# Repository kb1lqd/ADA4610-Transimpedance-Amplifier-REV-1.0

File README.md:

Notes

# 2022-08-23

* Soldered the board together
* It works! But I did find some minor errors.
* The voltage output varies as expected with light over a wide range

## Errors
* D1 footprint pin 1 assingment is backwards, this resulted in the diode being backwards
* The resulting current from the device is quite large resulting in the second amplifier stage being saturate in a lit room, I removed R7 to create a voltage follower and this alleviate the issues for now
* Placing the output on a scope it's clear there is a HF oscillation at 2.24mHz
** NOTE that the oscillation appears to be only on the 2nd stage output and not the first stage. Note that the second stage is now a voltage follower

# 2022-08-24

* Placed a 33pF capacitor across R8 and this stopped the oscillation
* I repopulated R7 with a 1K resistor
* There is some very very high frequency noise but pretty negligable it seems
* It works! I can definetley see an IRDA remote control signal at ~37KHz carrier
* It seems like if I want to use this in a bright room I'm going to have to turn the gains down
** Which is better - the TIA or the second stage?

# 2022-10-03

I've built up a bit of infrastructure around this TIA:
* Headphone amplifier to output the audio frequencies directly into headphones
* Listened to external light sources with a len assembly 3 miles away
* Built a simple audio light transmitter

I've noticed a faire bit of noise in the circuit. Hooking a scope up to the TP output I see a fairly complex oscillation between 30KHz and 97KHz. There is a different noise on the TIA output directly much smaller prior to the line driver amplifier.

**Noise on the TIA PCB 50 Ohm Output***

**Noise on the TIA Output directly**

I can see and hear the 120 Hz hum from my indoor (dim) lights that this noise is on top of.

# 2022-10-04

* I put the recommended bulk capacitors on the PYBE20-Q24-D5-T - No significant change but leaving them There
* I think it may have knocked a bit of the switching noise off
  * I defintely see a 32KHz DC/DC switching noise but it's near my scopes limit
  * It is seen on the preamp section op-amp bulk capacitors and in the TIA signal itself - It may be ground noise coming through the GND clip...?
  * Placing bulk capacitance on the preamp - no effect
* I added a 15pF capacitor to C2 to help bypass any HF signals past the 0 ohm or stabalize the POS input when in a higher impedance configuration
* I changed the Cf on the TIA (C4) from 3.3pF to 33pF for improved stability - No significant change - The nosie see is the same and defintely switching noise (likley on GND)
* I iterated a Cf across R8 and found that a 1nF completely kills the oscillation see - Tried ~200pF with good results but sign reduced from ~300mV to 60mV peak to peak.

I'm getting subjectively reduced noise!

I can clearly head music and tones from an online frequency generator through the transmitter (Although I don't think it's fully modulating the LED)

I listened to a few signals:

**iPhone FaceID Pulses**

The pulses are very clear (DC Coupled scope after the DC blocking capacitor) with a rise time of 92us (~3KHz)

**Optical Mouse LED/LASER**

This was much quicker of a signal and measured around 3.6us which is approximately (0.35/Tr) 100KHz bandwidth. I don't know what this signal looks linear.

# 2022-12-26

* I soldered a new TIA PCB together (Ver1.1) with just U1 TIA. I found that the TIA was stable at RF=10K and CF=6.6pF with the diode in photovoltaic mode (grounded) and the TIA V+ referenced to GND. This configuration did require U1 to operate with a split rail.
* I was wrong in the prior testing and it seemed that the U2 second stage was LPF'ing the 37KHz IRDA signals. I was clearly able to see the IRDA waveforms (still looked RC charged/discharged but that might have been the IR remote itself - More investigation needed.

# To-Do
* [DONE] Track down oscillation
* [DONE] Detect light pulses in the scope and observe the results
* Detemirne rough frequency response - even if simulated with updated values (37KHz carrier pulses looked pretty rounded) - This may inform a reduction in capacitances or resistances)

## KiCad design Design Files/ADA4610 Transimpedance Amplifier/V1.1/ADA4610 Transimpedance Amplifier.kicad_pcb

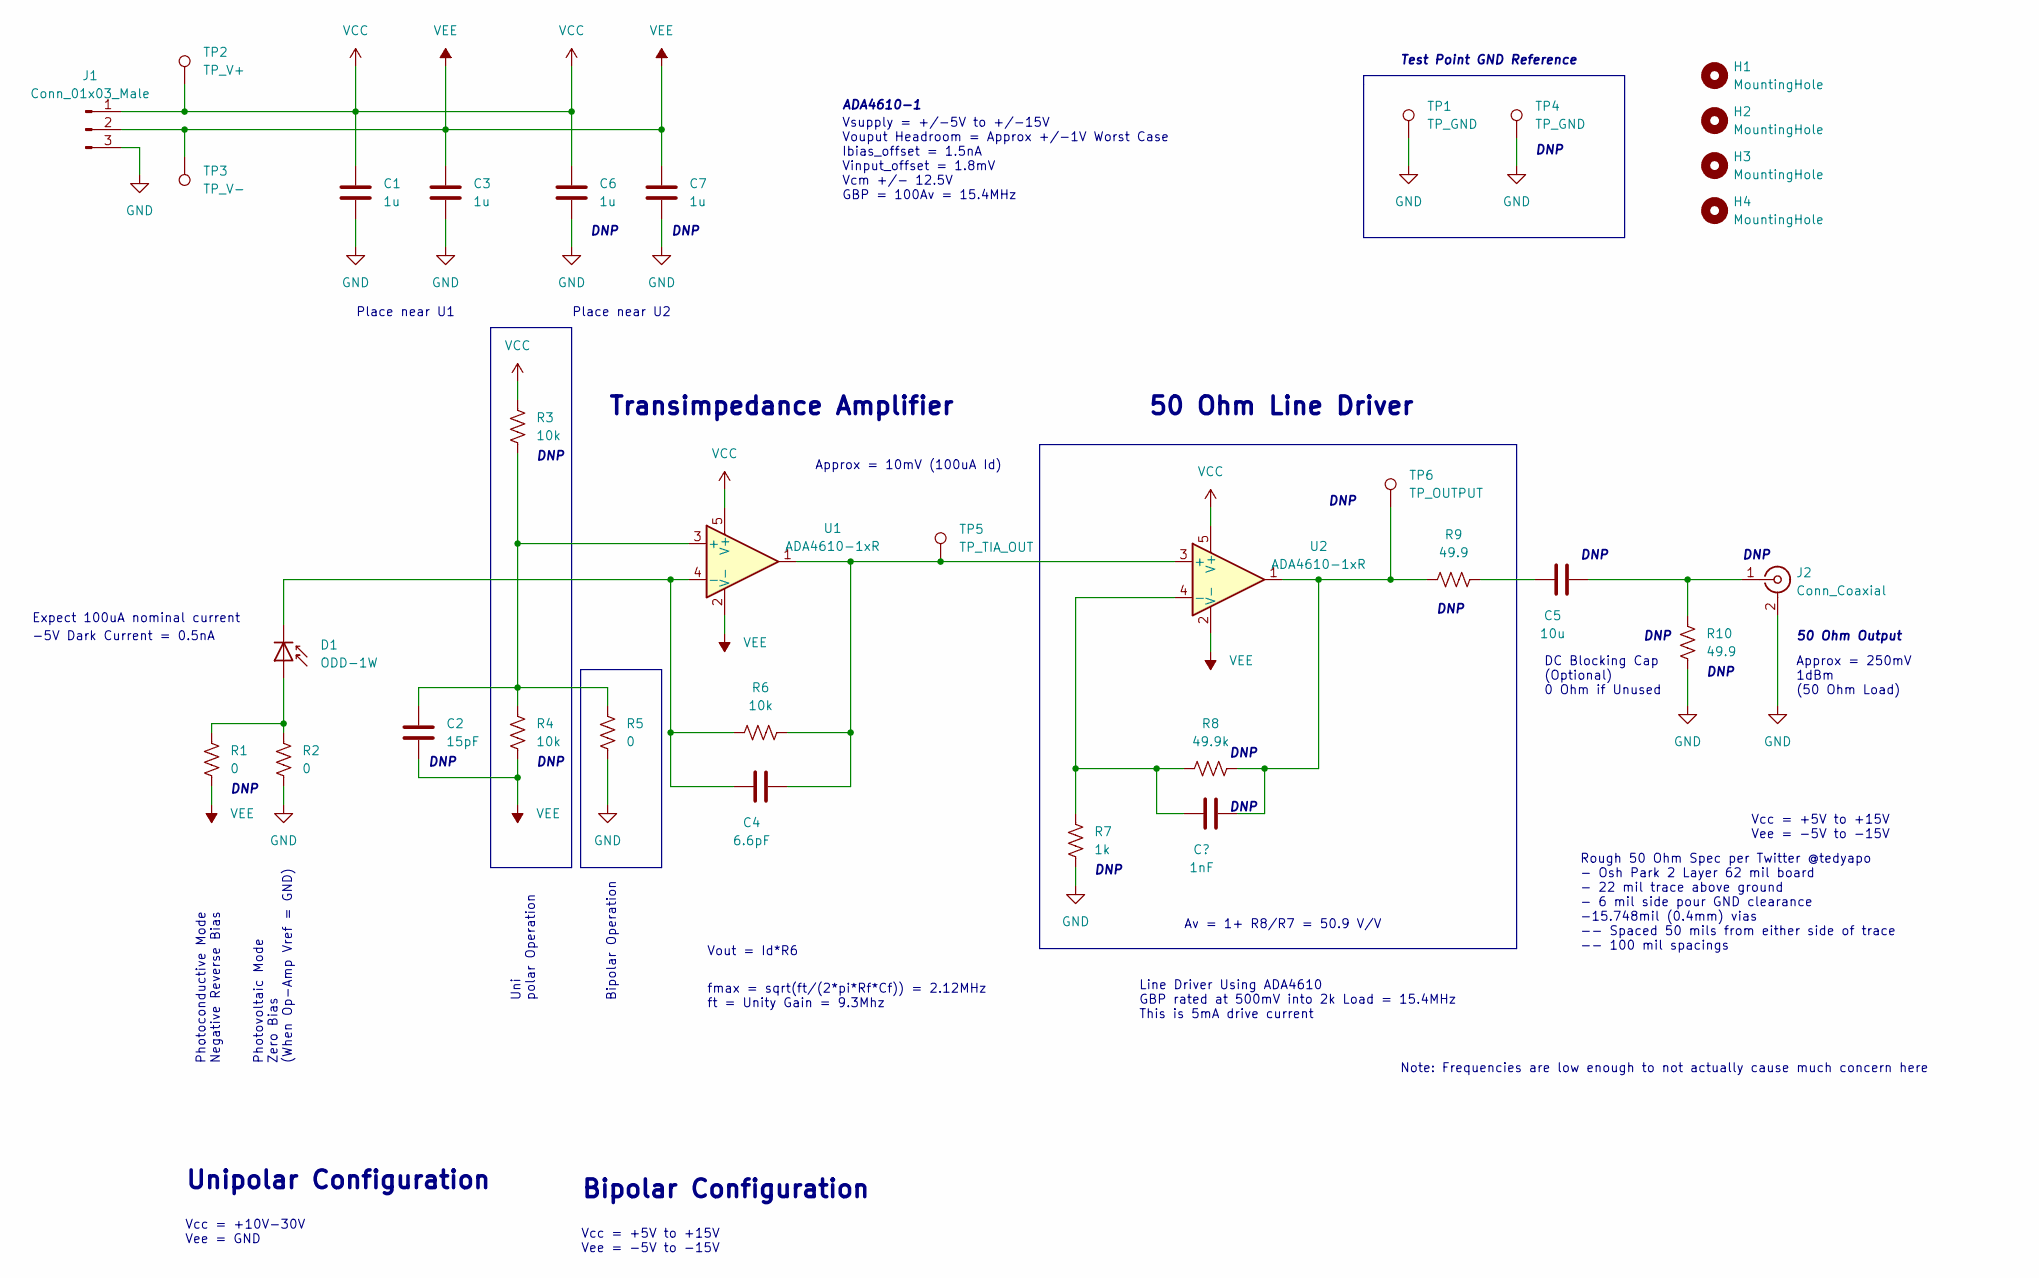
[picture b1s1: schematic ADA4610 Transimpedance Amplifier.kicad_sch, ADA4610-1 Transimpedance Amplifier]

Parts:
C1, C3, C6, C7: 1u; C_1206_3216Metric_Pad1.33x1.80mm_HandSolder
C2: 15pF; C_0805_2012Metric_Pad1.18x1.45mm_HandSolder
C4: 6.6pF; C_0603_1608Metric_Pad1.08x0.95mm_HandSolder
C5: 10u; C_1210_3225Metric_Pad1.33x2.70mm_HandSolder
D1: ODD-1W; TO-18-2_Lens_Centered
H1, H2, H3, H4: MountingHole; MountingHole_4.3mm_M4
J1: Conn_01x03_Male; Molex_KK-254_AE-6410-03A_1x03_P2.54mm_Vertical
J2: Conn_Coaxial; RFSOLUTIONS_CON-SMA-EDGE-S
R1, R2, R5: 0; R_0603_1608Metric_Pad0.98x0.95mm_HandSolder
R3, R4: 10k; R_0603_1608Metric_Pad0.98x0.95mm_HandSolder
R6: 10k; R_0805_2012Metric_Pad1.20x1.40mm_HandSolder
R7: 1k; R_0603_1608Metric_Pad0.98x0.95mm_HandSolder
R8: 49.9k; R_0805_2012Metric_Pad1.20x1.40mm_HandSolder
R9, R10: 49.9; R_0805_2012Metric_Pad1.20x1.40mm_HandSolder
TP1, TP4: TP_GND; TestPoint_Keystone_5010-5014_Multipurpose
TP2: TP_V+; TestPoint_Keystone_5010-5014_Multipurpose
TP3: TP_V-; TestPoint_Keystone_5010-5014_Multipurpose
TP5: TP_TIA_OUT; TestPoint_Keystone_5010-5014_Multipurpose
TP6: TP_OUTPUT; TestPoint_Keystone_5010-5014_Multipurpose
U1, U2: ADA4610-1xR; SOT-23-5

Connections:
GND: C1.1, C3.1, C6.1, C7.1, J1.3, J2.2 (Ext), R2.2, R5.2, R7.1, R10.2, TP1.1, TP4.1
unnamed: C2.2, R3.2, R4.1, R5.1, U1.3 (+)
unnamed: C4.1, D1.1 (K), R6.1, U1.4 (-)
unnamed: C4.2, R6.2, TP5.1, U1.1, U2.3 (+)
unnamed: C5.1, R9.1
unnamed: C5.2, J2.1 (In), R10.1
unnamed: D1.2 (A), R1.1, R2.1
unnamed: R7.2, R8.2, U2.4 (-)
unnamed: R8.1, R9.2, TP6.1, U2.1
VCC: C1.2, C6.2, J1.1, R3.1, TP2.1, U1.5 (V+), U2.5 (V+)
VEE: C2.1, C3.2, C7.2, J1.2, R1.2, R4.2, TP3.1, U1.2 (V-), U2.2 (V-)

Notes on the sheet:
50 Ohm Output
Uni polar Operation
50 Ohm Line Driver
DNP
DC Blocking Cap (Optional) 0 Ohm if Unused
Approx = 10mV (100uA Id)
Note: Frequencies are low enough to not actually cause much concern here
Vcc = +5V to +15V Vee = -5V to -15V
Line Driver Using ADA4610 GBP rated at 500mV into 2k Load = 15.4MHz This is 5mA drive current
Unipolar Configuration
Rough 50 Ohm Spec per Twitter @tedyapo - Osh Park 2 Layer 62 mil board - 22 mil trace above ground - 6 mil side pour GND clearance -15.748mil (0.4mm) vias -- Spaced 50 mils from either side of trace -- 100 mil spacings
Bipolar Operation
fmax = sqrt(ft/(2*pi*Rf*Cf)) = 2.12MHz ft = Unity Gain = 9.3Mhz
Vsupply = +/-5V to +/-15V Vouput Headroom = Approx +/-1V Worst Case Ibias_offset = 1.5nA Vinput_offset = 1.8mV Vcm +/- 12.5V GBP = 100Av = 15.4MHz
ADA4610-1
Test Point GND Reference
Place near U2
Vout = Id*R6
Photovoltaic Mode Zero Bias (When Op-Amp Vref = GND)
Photoconductive Mode Negative Reverse Bias
Expect 100uA nominal current
Transimpedance Amplifier
Av = 1+ R8/R7 = 50.9 V/V
Bipolar Configuration
-5V Dark Current = 0.5nA
Approx = 250mV 1dBm (50 Ohm Load)
Vcc = +10V-30V Vee = GND
Place near U1

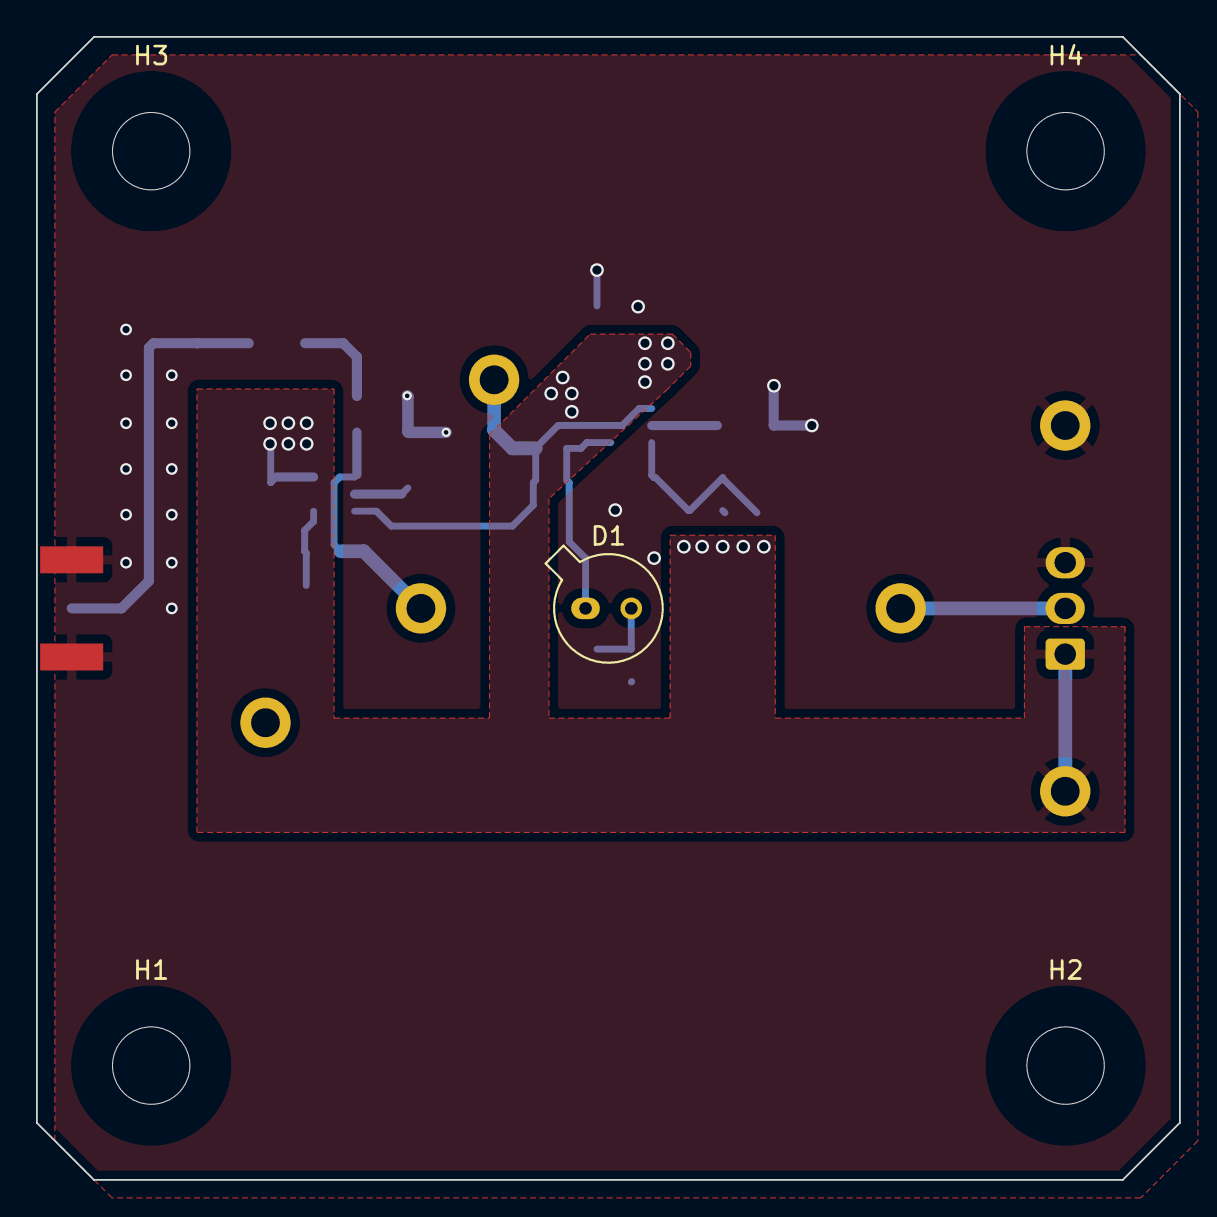
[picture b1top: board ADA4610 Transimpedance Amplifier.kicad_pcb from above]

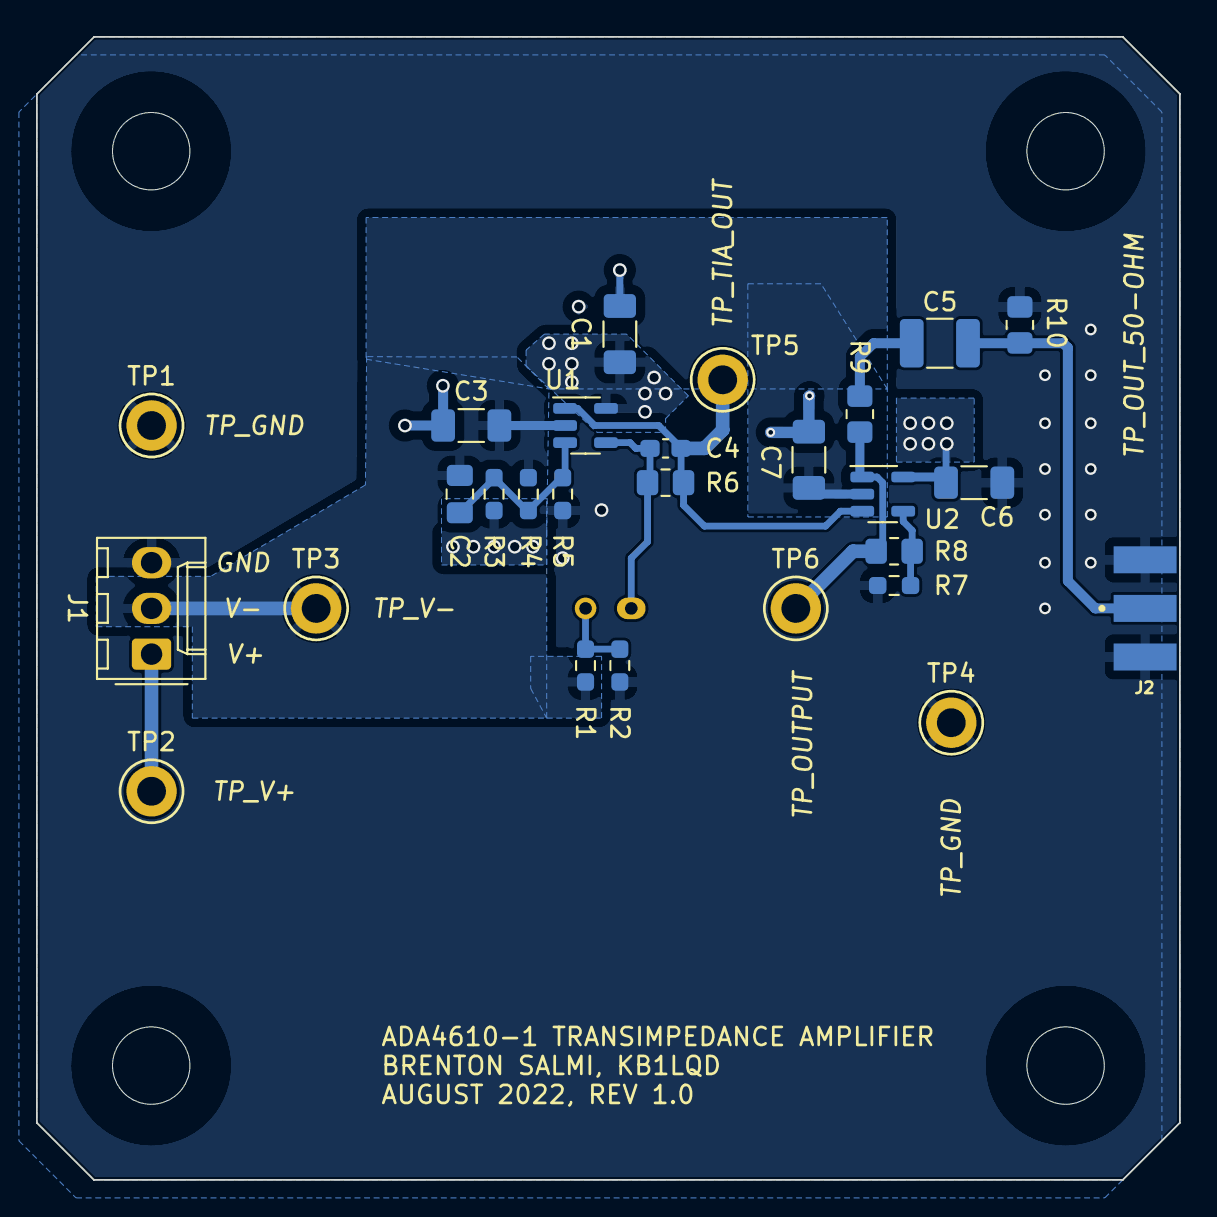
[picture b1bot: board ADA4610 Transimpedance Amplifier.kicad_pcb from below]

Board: 2 copper layers, 63.5 x 63.5 mm, 32 parts (27 on the bottom side), 11 nets.

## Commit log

2022-08-07 Initial commit.
    Basic transimpedance amplifier and line driver.
2022-08-07 Initial pass finished.
    Finished the initial schematic and scope. Also did some simulations. Google drive has the dBm output calculations.
2022-08-08 Assigned most footprints - picked parts.
2022-08-08 All components and footprints assigned and created. Layout imported parts.
2022-08-09 Imported Mcmaster carr shelving brackets for an initial fit.
2022-08-09 Gave a quick schematic review
2022-08-09 Initial Placement Done.
2022-08-09 Placement and text completed.
    Ready for traces.
2022-08-10 Updated PCB to osh park 2 layer rules.
2022-08-10 Board completed and no errors.
2022-08-10 Ordered.
2022-08-23 Built unit and took notes
    Works! Some issues but mostly resolved.
2022-08-25 Update README.md
    Working PCBA updates.
2022-08-27 Adding old pcb optical comm reuse plan.
2022-08-27 Adding as built TPA611A2 audio amp.
2022-10-03 Updating information.
2022-10-03 Fixed images.
2022-10-05 Fixed oscillation issues in TIA.
2022-12-27 Old commit + V1.1
    Building a second board with V1.1 configuration. I updated the schematics to reflect this change.
2022-12-28 commit as built 2022-12-27
    As built, working with +5V unipolar and ~100x second stage gain. IRDA signals clearly visible at 37KHz.
2023-05-16 Adding frontend pdf.
    Adding frontend pdf.
